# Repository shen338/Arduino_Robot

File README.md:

# Arduino Controlled Autonomous Robot for Ball Collection
In this project, we do the following things:  
· Employed Pixy Camera and image segmentation algorithm to locate the ball and container in real time  
· Wrote PID algorithm for the robot to track and follow the ball, programmed in Arduino IDE  
· Collaborated on the design and fabrication the robots powertrain, sensor and navigation hardware  

### Two demo ball tracking videos and our performance in final competition

[Final Competition](https://www.youtube.com/watch?v=fU1fNfBJTtA)   
[Ball Tracking Demo 1](https://www.youtube.com/watch?v=Wlfwm1OvA4c)  
[Ball Tracking Demo 2](https://www.youtube.com/watch?v=8-BpY_hJBjg)  

### Appearance of our robot: 

### Appearance of our container: 

#### All the source code is in the code/Master folder.

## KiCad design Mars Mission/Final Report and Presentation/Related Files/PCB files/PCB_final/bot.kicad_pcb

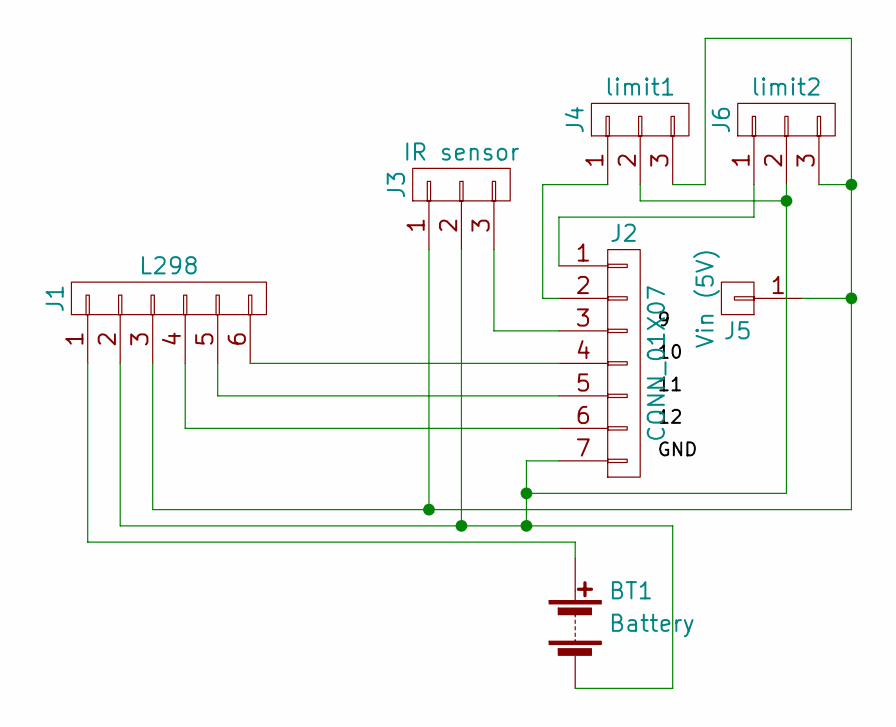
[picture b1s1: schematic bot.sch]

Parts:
BT1: Battery; Pin_Header_Straight_2x01_Pitch2.54mm
J1: L298; Pin_Header_Straight_1x06_Pitch2.54mm
J2: CONN_01X07; Pin_Header_Straight_1x07_Pitch2.54mm
J3: IR sensor; Pin_Header_Straight_1x03_Pitch2.54mm
J4: limit1; Pin_Header_Straight_1x03_Pitch2.54mm
J5: Vin (5V); Pin_Header_Straight_1x01_Pitch2.54mm
J6: limit2; Pin_Header_Straight_1x03_Pitch2.54mm

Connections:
unnamed: BT1.1 (+), J1.1
unnamed: BT1.2 (-), J1.2, J2.7, J3.2, J4.2, J6.2
unnamed: J1.3, J3.1, J4.3, J5.1, J6.3
unnamed: J1.4, J2.6
unnamed: J1.5, J2.5
unnamed: J1.6, J2.4
unnamed: J2.1, J6.1
unnamed: J2.2, J4.1
unnamed: J2.3, J3.3

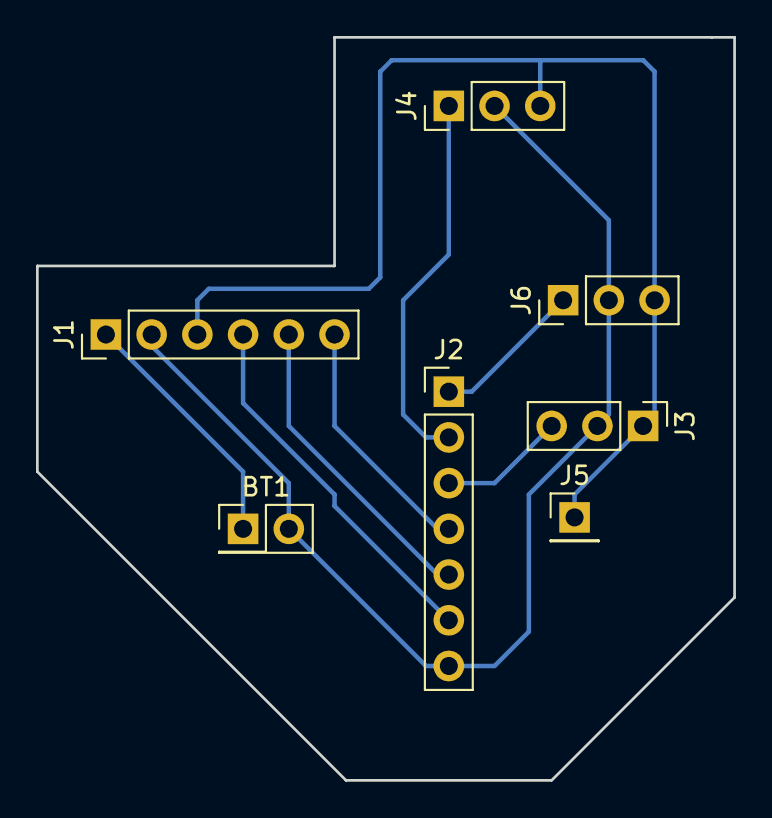
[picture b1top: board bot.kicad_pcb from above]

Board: 2 copper layers, 38.7 x 41.3 mm, 7 parts (0 on the bottom side), 9 nets.
